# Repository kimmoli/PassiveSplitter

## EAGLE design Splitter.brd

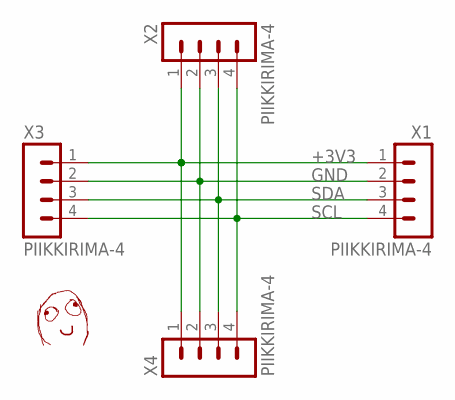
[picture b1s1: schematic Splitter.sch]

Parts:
U$1: DAFUG
X1, X2, X3, X4: PIIKKIRIMA-4

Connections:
+3V3: X1.1, X2.1, X3.1, X4.1
GND: X1.2, X2.2, X3.2, X4.2
SCL: X1.4, X2.4, X3.4, X4.4
SDA: X1.3, X2.3, X3.3, X4.3

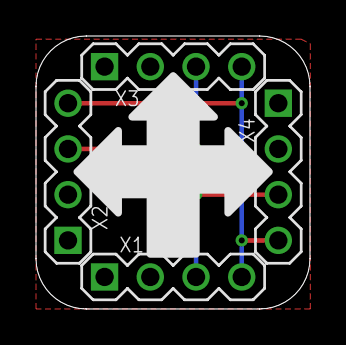
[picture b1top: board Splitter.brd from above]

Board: 2 copper layers, 15.2 x 15.2 mm, 5 parts (1 on the bottom side), 4 nets.
